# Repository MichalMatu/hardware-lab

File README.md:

# Hardware Lab

Hardware experiments, firmware starters, board bring-up projects and setup notes.

This repository consolidates several previously standalone repositories while retaining their Git history. Each project remains isolated in its own directory under `projects/`.

## Projects

- `projects/esp_rs` — ESP Rust experiments and starter firmware
- `projects/rp_pi2_zero` — Raspberry Pi Zero 2 W setup and experiments
- `projects/modules` — ESP32-family module experiments
- `projects/esp32s3-edge-ai` — modular ESP32-S3 edge AI experiments (scaffold only)
- `projects/nrf52840` — nRF52840 SuperMini / nice!nano experiments
- `projects/LilyGo_4.7` — LilyGo T5 4.7-inch e-paper firmware
- `projects/milkV256mb` — Milk-V Duo 256 setup and experiments
- `projects/LILYGO_T_HIGH_GROW` — LILYGO T-HIGrow PlantStatus firmware and web UI (sanitized snapshot)
- `projects/esp32-cam-telegram` — ESP32-CAM/OV2640 Telegram motion camera (unfinished; build validated)
- `projects/esp32_s2_wifi` — ESP32-S2 USB NCM ↔ Wi-Fi bridge; working main snapshot plus preserved OLED variant
- `projects/pcb` — SKiDL/KiCad PCB workspace and board experiments (unfinished; hardware validation pending)
- `projects/esp32_c6_zigbee` — retired ESP32-C6 Zigbee/low-level I/O extension prototype; maintained code absorbed into esp32s3_LiteGraph

- `projects/IPCam` — IP camera/YOLO detection and recording experiment (clean snapshot)
- `projects/body-conductor-mvp` — MediaPipe body-to-audio mapping experiment (clean snapshot)

- `projects/kobra2-neo` — Anycubic Kobra 2 Neo modular three-axis platform: interchangeable pen, clay/paste and future toolheads

## History and licenses

Most imported projects retain their original commits as merge ancestry. Some former standalone repositories have since been removed after verification. Projects with contaminated secret history may be imported as sanitized snapshots instead. Existing per-project license files and notices remain authoritative for their respective project directories; there is intentionally no repository-wide license override.

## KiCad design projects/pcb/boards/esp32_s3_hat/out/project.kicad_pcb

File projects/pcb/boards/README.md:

# boards/

Ten katalog zawiera tylko aktywne warianty PCB rodziny Growclip.

Po cleanupie stare eksperymenty zostaly przeniesione do `../archive/boards/`. Nie ma jeszcze boardu oznaczonego jako produkcyjny.

Zasady aktywnego boardu sa opisane w `BOARD_CONTRACT.md`.

## Planowane pierwsze warianty

- `growclip_s3_basic` - prosty HAT do profilu S3,
- `growclip_c6_basic` - prosty HAT do profilu C6.

Aktualne profile-kandydaci w `../hosts/` bazuja na oficjalnych Espressif DevKitC-1, ale pozostaja `draft`, dopoki nie potwierdzimy zgodnosci z fizycznymi plytkami przeznaczonymi do Growclip.

Nie tworzymy boardu jako kopii hosta. Board wskazuje host profile i korzysta z jego `pinout.toml` oraz `mechanical.toml`.

## Zasada

Board powinien byc cienka kompozycja:
- host profile,
- zero lub kilka reusable modules,
- tylko board-specific polaczenia i layout.

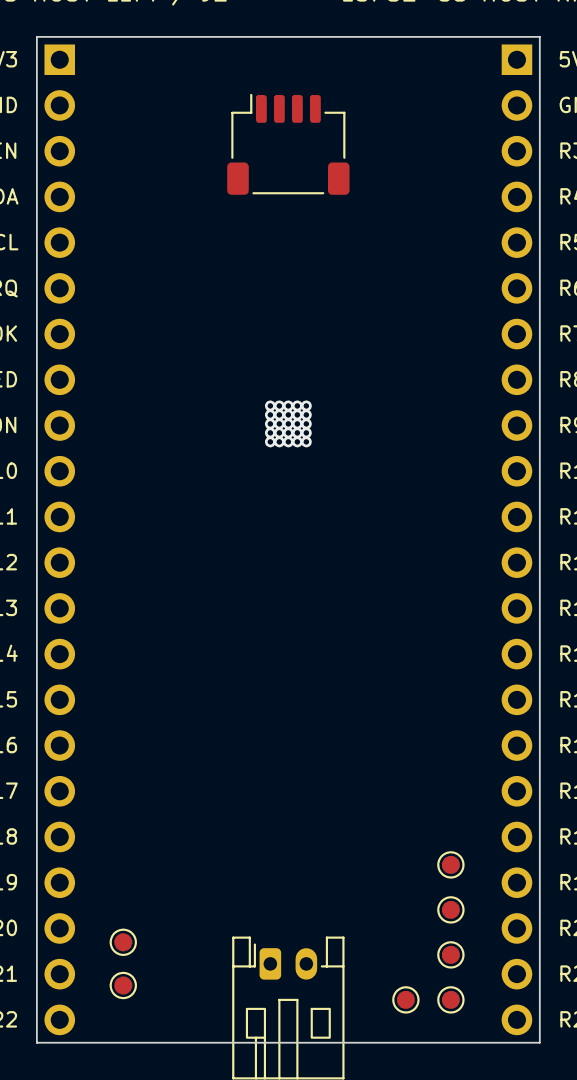
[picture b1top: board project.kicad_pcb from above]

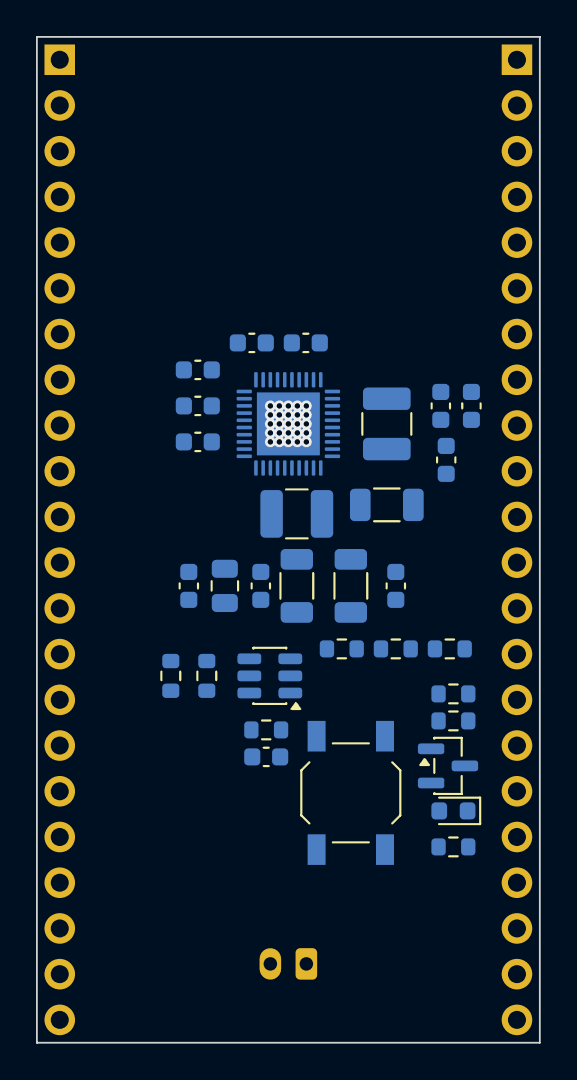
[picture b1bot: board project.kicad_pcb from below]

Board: 4 copper layers, 27.9 x 55.9 mm, 43 parts (32 on the bottom side), 24 nets, no tracks yet.

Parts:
C_DCDC1: 22uF; C_1206_3216Metric
C_PMIC_ALDOIN: 2.2uF; C_0603_1608Metric
C_PMIC_BAT: 1uF; C_0603_1608Metric
C_PMIC_BLDOIN: 2.2uF; C_0603_1608Metric
C_PMIC_SYSA: 22uF; C_1206_3216Metric
C_PMIC_SYSB: 22uF; C_1206_3216Metric
C_PMIC_VBUSA: 10uF; C_0805_2012Metric
C_PMIC_VBUSB: 2.2uF; C_0603_1608Metric
C_PMIC_VIN1, C_PMIC_VIN2, C_PMIC_VIN3, C_PMIC_VIN4: 2.2uF; C_0603_1608Metric
C_PMIC_VMID: 2.2uF; C_0603_1608Metric
C_PMIC_VREF: 1uF; C_0603_1608Metric
C_PMIC_VRTC: 2.2uF; C_0603_1608Metric
C_PWRON: 1nF; C_0603_1608Metric
D_CHG: CHG; LED_0603_1608Metric
J_BAT: Conn_01x02; JST_PH_S2B-PH-K_1x02_P2.00mm_Horizontal
J_HOST_L: Conn_01x22; PinSocket_1x22_P2.54mm_Vertical
J_HOST_R: Conn_01x22; PinSocket_1x22_P2.54mm_Vertical
J_QWIIC: Conn_01x04; JST_SH_SM04B-SRSS-TB_1x04-1MP_P1.00mm_Horizontal
L_DCDC1: 1uH; L_1210_3225Metric
L_PMIC_SW: 1uH; L_1210_3225Metric
Q_CHG: 2N7002; SOT-23
R_CHG_G: 100R; R_0603_1608Metric
R_CHG_PD: 100k; R_0603_1608Metric
R_HOST_3V3_OFF: 100R; R_0603_1608Metric
R_HOST_3V3_ON: 100k; R_0603_1608Metric
R_I2C_SCL, R_I2C_SDA: 2.2k; R_0603_1608Metric
R_LED_CHG: 1k; R_0603_1608Metric
R_PMIC_IRQ: 4.7k; R_0603_1608Metric
R_PWRON: 510R; R_0603_1608Metric
SW_PWRON: SW_Push; SW_SPST_TL3342
TP_GND: TestPoint; TestPoint_Pad_D1.0mm
TP_PWRON: TestPoint; TestPoint_Pad_D1.0mm
TP_TS: TestPoint; TestPoint_Pad_D1.0mm
TP_VMID: TestPoint; TestPoint_Pad_D1.0mm
TP_VREF: TestPoint; TestPoint_Pad_D1.0mm
TP_VRTC: TestPoint; TestPoint_Pad_D1.0mm
TP_VSYS: TestPoint; TestPoint_Pad_D1.0mm
U_HOST_3V3_SW: TPS22917L; SOT-23-6
U_PMIC: AXP2101; VQFN-40-1EP_5x5mm_P0.4mm_EP3.5x3.5mm

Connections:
AXP_PWRON: C_PWRON.1, R_PWRON.1, TP_PWRON.1, U_PMIC.30
BAT_RAW_VCC: C_PMIC_BAT.1, J_BAT.1, U_PMIC.33
BAT_TS: TP_TS.1, U_PMIC.31
CHG_LED_GATE: Q_CHG.1, R_CHG_G.2, R_CHG_PD.1
ESP_3V3: J_HOST_L.1, R_I2C_SCL.1, R_I2C_SDA.1, R_PMIC_IRQ.1, U_HOST_3V3_SW.1
ESP_5V: C_PMIC_VBUSA.1, C_PMIC_VBUSB.1, J_HOST_R.1, R_HOST_3V3_OFF.1, U_PMIC.37
ESP_GPIO21_SDA: J_HOST_L.4, J_QWIIC.3, R_I2C_SDA.2, U_PMIC.39
ESP_GPIO22_SCL: J_HOST_L.5, J_QWIIC.4, R_I2C_SCL.2, U_PMIC.40
ESP_GPIO25: J_HOST_L.8, R_CHG_G.1, U_PMIC.1
ESP_GPIO27: J_HOST_L.9, R_PWRON.2, SW_PWRON.1
ESP_GPIO32: J_HOST_L.6, R_PMIC_IRQ.2, U_PMIC.38
ESP_GPIO33: J_HOST_L.7, U_PMIC.29
GND: C_DCDC1.2, C_PMIC_ALDOIN.2, C_PMIC_BAT.2, C_PMIC_BLDOIN.2, C_PMIC_SYSA.2, C_PMIC_SYSB.2, C_PMIC_VBUSA.2, C_PMIC_VBUSB.2, C_PMIC_VIN1.2, C_PMIC_VIN2.2, C_PMIC_VIN3.2, C_PMIC_VIN4.2, C_PMIC_VMID.2, C_PMIC_VREF.2, C_PMIC_VRTC.2, C_PWRON.2, J_BAT.2, J_HOST_L.2, J_HOST_R.2, J_QWIIC.1, Q_CHG.2, R_CHG_PD.2, R_HOST_3V3_ON.2, SW_PWRON.2, TP_GND.1, U_HOST_3V3_SW.5, U_PMIC.3, U_PMIC.41
HAT_3V3: C_DCDC1.1, J_QWIIC.2, L_DCDC1.2, U_HOST_3V3_SW.6, U_PMIC.21
HAT_3V3_SW: L_DCDC1.1, U_PMIC.22
HOST_3V3_SW_CTRL: R_HOST_3V3_OFF.2, R_HOST_3V3_ON.1, U_HOST_3V3_SW.3
unnamed: D_CHG.2, R_LED_CHG.2
unnamed: D_CHG.1, Q_CHG.3
PMIC_SW: L_PMIC_SW.1, U_PMIC.35
PMIC_VMID: C_PMIC_VMID.1, TP_VMID.1, U_PMIC.36
PMIC_VREF: C_PMIC_VREF.1, TP_VREF.1, U_PMIC.2
PMIC_VRTC: C_PMIC_VRTC.1, TP_VRTC.1, U_PMIC.27, U_PMIC.28
PMIC_VSYS: C_PMIC_ALDOIN.1, C_PMIC_BLDOIN.1, C_PMIC_SYSA.1, C_PMIC_SYSB.1, C_PMIC_VIN1.1, C_PMIC_VIN2.1, C_PMIC_VIN3.1, C_PMIC_VIN4.1, L_PMIC_SW.2, R_LED_CHG.1, TP_VSYS.1, U_PMIC.6, U_PMIC.7, U_PMIC.13, U_PMIC.17, U_PMIC.23, U_PMIC.24, U_PMIC.34
__NOCONNECT: U_PMIC.4, U_PMIC.5, U_PMIC.8, U_PMIC.9, U_PMIC.10, U_PMIC.11, U_PMIC.12, U_PMIC.14, U_PMIC.15, U_PMIC.16, U_PMIC.18, U_PMIC.19, U_PMIC.20, U_PMIC.25, U_PMIC.26, U_PMIC.32

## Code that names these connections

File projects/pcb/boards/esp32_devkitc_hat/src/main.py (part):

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    ("ESP_GPIO39_VN", "VN"),
    ("ESP_GPIO34", "IO34"),
    ("ESP_GPIO35", "IO35"),
    ("ESP_GPIO32", "IO32"),
    ("ESP_GPIO33", "IO33"),
    ("ESP_GPIO25", "IO25"),
    ("ESP_GPIO26", "IO26"),
    ("ESP_GPIO27", "IO27"),
    ("ESP_GPIO14", "IO14"),
    ("ESP_GPIO12", "IO12"),
    ("GND", "GND"),
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RIGHT_HOST_PINS = [
    ("GND", "GND"),
    ("ESP_GPIO23_MOSI", "IO23"),
    ("ESP_GPIO22_SCL", "IO22"),
    ("ESP_UART0_TX", "TX"),
    ("ESP_UART0_RX", "RX"),
    ("ESP_GPIO21_SDA", "IO21"),
    ("GND", "GND"),
    ("ESP_GPIO19_MISO", "IO19"),
    ("ESP_GPIO18_SCK", "IO18"),
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    _add_host_3v3_auto_switch(hat_pwr.vcc, host_3v3.vcc, host_5v.vcc, gnd)

    i2c0 = SimpleNamespace(
        sda=_get_or_create_net(nets, "ESP_GPIO21_SDA"),
        scl=_get_or_create_net(nets, "ESP_GPIO22_SCL"),
    )

    irq = _get_or_create_net(nets, "ESP_GPIO32")
    pwrok = _get_or_create_net(nets, "ESP_GPIO33")
    chgled = _get_or_create_net(nets, "ESP_GPIO25")
    pwron_btn = _get_or_create_net(nets, "ESP_GPIO27")
    pwron = _get_or_create_net(nets, "AXP_PWRON")
    ts = _get_or_create_net(nets, "BAT_TS")

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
